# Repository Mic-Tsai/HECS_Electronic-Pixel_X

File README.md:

## HECS Electronic | Pixel-X
### Light Painting Equipment

2013 | HECS

We are a visual team of POI arty performers. Design and develop the light-painting equipment which contains picture & dynamic presentation. This was my college side project during 2013-2014 in KUAS (National Kaohsiung University of Applied Sciences, Taiwan).

- [Promotional Video](https://youtu.be/c2NhDoxItCM)

**2017 | Pixel-X**

  **Re-engineering hardware part, split the core as controller and display, purpose to minimum PCB after-assemble space. LEDs used the improved version SK6812B-3535 (package) from WS2812B-5050, got better heat radiating, the smaller dots will increase the image resolution.**

```
Arduino tool kit, and require the following material:
- MCU: ATmega328p
- Storage: SD card
- Display: SK6812B-3535
- Power source: Li-Po Battery
``` 

## 

### **About Mic**

Director of HECS, design light painting product that contains hardware layout and software programming.

- [Resume](https://drive.google.com/file/d/1NEWwNo3X4ogJMNzp6jpFyT0a6GPGhs7Q/view)
## 

### **About HECS**

Interesting how it work please refer for detail:

- [HECS ISSUU](https://issuu.com/56905554/docs/hecs_book)

- [HECS ISSUU moble device](https://issuu.com/56905554/docs/hecs-book_issuu)

- [HECS Electronics](https://drive.google.com/file/d/1tgr780FQ_Ib0JO3FdQn_M6LVbDeVmUmG/view?usp=sharing)
## 

### **About Hardware**

If you want to buy this board and are in Taiwan, please visit my shop: 

Will OPEN SOON:
* [HECS SHOP](https://www.)
* Contact me via mail (xbcke12345@gmail.com)
* If this project helping. Please generously support =)

## 

## 

>### License Information
>>This product is open source! Both, our hardware and software are open source and licensed under the following:
>>#### Hardware
>>>All hardware is released under [Creative Commons Share-alike 4.0 International](http://creativecommons.org/licenses/by-sa/4.0/).
>>#### Software 
>>>All software is released under the MIT License [http://opensource.org/licenses/MIT](http://opensource.org/licenses/MIT).
>>#### Documentation
>>>The documentation on this page is released under [Creative Commons Share-alike 4.0 International](http://creativecommons.org/licenses/by-sa/4.0/).

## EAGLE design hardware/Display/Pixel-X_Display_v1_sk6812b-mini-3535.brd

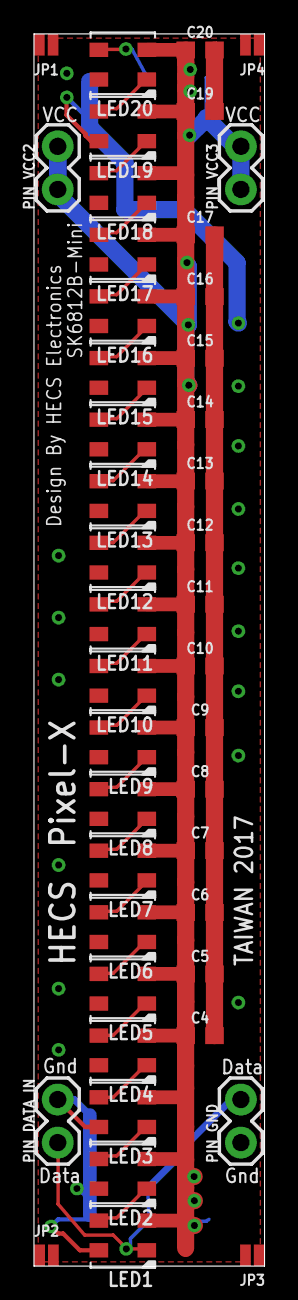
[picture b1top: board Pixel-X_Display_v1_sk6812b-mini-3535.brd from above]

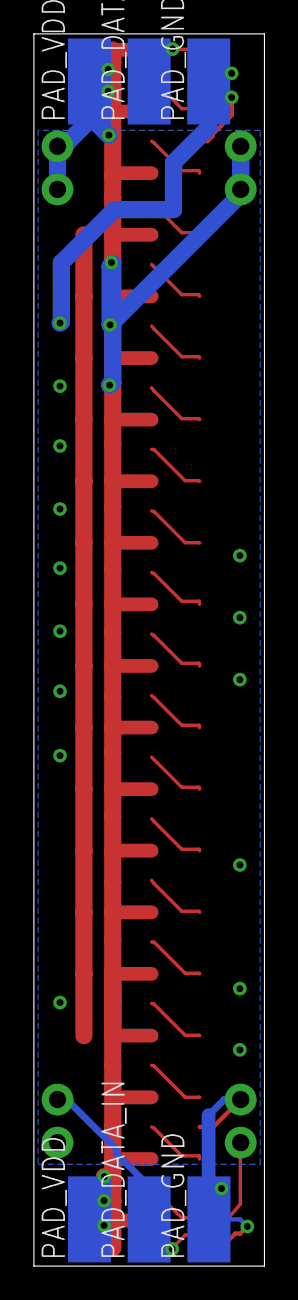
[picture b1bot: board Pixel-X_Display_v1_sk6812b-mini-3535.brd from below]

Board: 2 copper layers, 13.6 x 72.7 mm, 50 parts (6 on the bottom side), 23 nets.

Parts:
C4, C5, C6, C7, C8, C9, C10, C11, C12, C13, C14, C15, C16, C17, C19, C20: 0.1uF; 0603
JP1, JP2, JP3, JP4: JUMPER-SMT_2_NO_NO-SILK; SMT-JUMPER_2_NO_NO-SILK
LED1, LED2, LED3, LED4, LED5, LED6, LED7, LED8, LED9, LED10, LED11, LED12, LED13, LED14, LED15, LED16, LED17, LED18, LED19, LED20: WS2812B3535; LED3535
PAD_DATA_IN: SMD2,54-5,08
PAD_DATA_OUT: SMD2,54-5,08
PAD_GND, PAD_GND1: SMD2,54-5,08
PAD_VDD, PAD_VDD1: SMD2,54-5,08
PIN_DATA_IN: 1X02
PIN_GND: 1X02
PIN_VCC2, PIN_VCC3: 1X02

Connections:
+5V: C4.1, C5.1, C6.1, C7.1, C8.1, C9.1, C10.1, C11.1, C12.1, C13.1, C14.1, C15.1, C16.1, C17.1, C19.1, C20.1, LED1.2, LED2.2, LED3.2, LED4.2, LED5.2, LED6.2, LED7.2, LED8.2, LED9.2, LED10.2, LED11.2, LED12.2, LED13.2, LED14.2, LED15.2, LED16.2, LED17.2, LED18.2, LED19.2, LED20.2, PAD_VDD.1, PAD_VDD1.1, PIN_VCC2.1, PIN_VCC2.2, PIN_VCC3.1, PIN_VCC3.2
COM: C4.2, C5.2, C6.2, C7.2, C8.2, C9.2, C10.2, C11.2, C12.2, C13.2, C14.2, C15.2, C16.2, C17.2, C19.2, C20.2, LED1.4, LED2.4, LED3.4, LED4.4, LED5.4, LED6.4, LED7.4, LED8.4, LED9.4, LED10.4, LED11.4, LED12.4, LED13.4, LED14.4, LED15.4, LED16.4, LED17.4, LED18.4, LED19.4, LED20.4, PAD_GND.1, PAD_GND1.1, PIN_DATA_IN.2, PIN_GND.1
unnamed: LED1.1, PAD_DATA_IN.1, PIN_DATA_IN.1, PIN_GND.2
unnamed: LED1.3, LED2.1
unnamed: LED2.3, LED3.1
unnamed: LED3.3, LED4.1
unnamed: LED4.3, LED5.1
unnamed: LED5.3, LED6.1
unnamed: LED6.3, LED7.1
unnamed: LED7.3, LED8.1
unnamed: LED8.3, LED9.1
unnamed: LED9.3, LED10.1
unnamed: LED10.3, LED11.1
unnamed: LED11.3, LED12.1
unnamed: LED12.3, LED13.1
unnamed: LED13.3, LED14.1
unnamed: LED15.3, LED16.1
unnamed: LED16.3, LED17.1
unnamed: LED17.3, LED18.1
unnamed: LED18.3, LED19.1
unnamed: LED19.3, LED20.1
unnamed: LED14.3, LED15.1
unnamed: LED20.3, PAD_DATA_OUT.1

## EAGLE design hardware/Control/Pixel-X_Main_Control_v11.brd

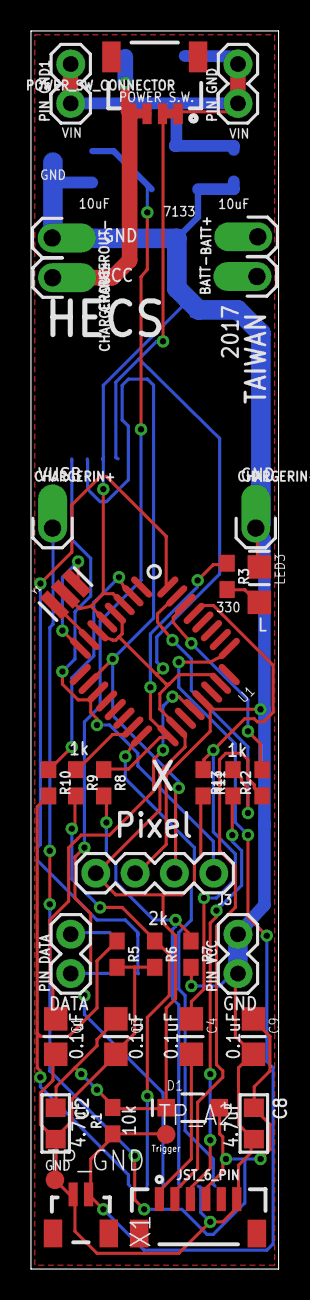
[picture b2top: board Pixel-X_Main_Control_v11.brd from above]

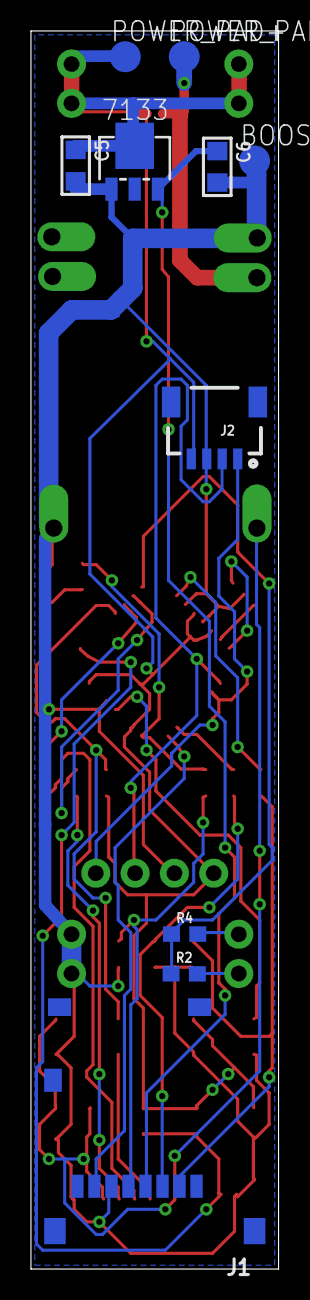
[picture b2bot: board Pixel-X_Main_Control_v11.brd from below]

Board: 2 copper layers, 16.0 x 80.0 mm, 47 parts (10 on the bottom side), 28 nets.

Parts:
7133: L78LXXCU/BU; SOT89
BATT+: 1X01_OFFSET
BATT-: 1X01_OFFSET
BOOSTOUT-: TPSQTP20R; TP20R
C1, C3, C4, C9: 0.1uF; CAP0805-NP
C2, C8: 4.7uF; C0805
C5, C6: 10uF; C0805
CHARGERIN+: 1X01_OFFSET
CHARGERIN-: 1X01_OFFSET
CHARGEROUT+: 1X01_OFFSET
CHARGEROUT-: 1X01_OFFSET
D1: MBR0520; SOD-123
J1: MICROSD_MOLEX_5025700893; 5025700893
J2: 1X04_1MM_RA
J3: 1X04
JST_6_PIN: JST_6_PIN_VERTICAL; JST-6-SMD-VERT-1.0MM
LED3: L_AMBER; LED0805
PIN_DATA: 1X02
PIN_GND, PIN_GND1: 1X02
PIN_VCC: 1X02
POWER_PAD+: TPSQTP20R; TP20R
POWER_PAD-: TPSQTP20R; TP20R
POWER_SW_CONNECTOR: 1X04_1MM_RA
R1: 10k; 0603
R2, R4: 120; 0603
R3: 330; 0603
R5, R6, R7: 2k; 0603
R8, R9, R10, R11, R12, R13: 1k; 0603
TP_A2: TPTP12R; TP12R
TP_GND: TPTP12R; TP12R
U1: ATMEGA328; QFP032
X1: BM02B-SRSS-TB
Y1: 16MHz; RESONATOR

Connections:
3V3OUT: 7133.3, C6.1, J1.P$4
+5V: 7133.4, C2.1, C3.1, C5.1, D1.1, J2.4, J3.4, PIN_GND.1, PIN_GND.2, PIN_GND1.1, PIN_GND1.2, POWER_PAD+.TP, POWER_SW_CONNECTOR.1, POWER_SW_CONNECTOR.2, R1.2, R11.2, U1.4, U1.6, U1.18, U1.23
A2: R1.1, TP_A2.TP, U1.25, X1.2
AREF: C1.1, U1.20
COM: 7133.1, BOOSTOUT-.TP, C1.2, C2.2, C3.2, C5.2, C6.2, C8.2, C9.2, CHARGERIN-.1, CHARGEROUT-.1, J1.P$6, J2.3, J3.3, JST_6_PIN.6, LED3.1, PIN_VCC.1, PIN_VCC.2, R5.2, R6.2, R7.2, TP_GND.TP, U1.3, U1.5, U1.21, X1.1, Y1.2
D0/RX: R12.2, U1.30
D1/TX: R13.2, U1.31
D2: R2.1, R4.1, U1.32
D4: R10.1, U1.2
D6: J2.2, J3.2, U1.10
D7: J2.1, J3.1, U1.11
D11/MOSI: R9.1, U1.15
D12/MISO: J1.P$7, U1.16
D13/SCK: R3.1, R8.1, U1.17
DTR: C4.1, R11.1, U1.29
unnamed: U1.8, Y1.3
unnamed: U1.7, Y1.1
unnamed: PIN_DATA.2, R4.2
unnamed: PIN_DATA.1, R2.2
unnamed: C4.2, JST_6_PIN.1
unnamed: LED3.2, R3.2
unnamed: J1.P$2, R5.1, R10.2
unnamed: J1.P$3, R6.1, R9.2
unnamed: J1.P$5, R7.1, R8.2
unnamed: CHARGEROUT+.1, POWER_PAD-.TP, POWER_SW_CONNECTOR.3, POWER_SW_CONNECTOR.4
RX: JST_6_PIN.2, R12.1
TX: JST_6_PIN.3, R13.1
VUSB: C8.1, C9.1, CHARGERIN+.1, D1.2, JST_6_PIN.4

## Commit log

2022-07-12 Code update 2022
    Add code v10 for Transfer & BTN function

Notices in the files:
parts and their libraries:
SparkFun-Connectors: Licensing: Creative Commons ShareAlike 4.0 International - https://creativecommons.org/licenses/by-sa/4.0
rc-master-smd: Copyright (C) 2007, Bob Starr
